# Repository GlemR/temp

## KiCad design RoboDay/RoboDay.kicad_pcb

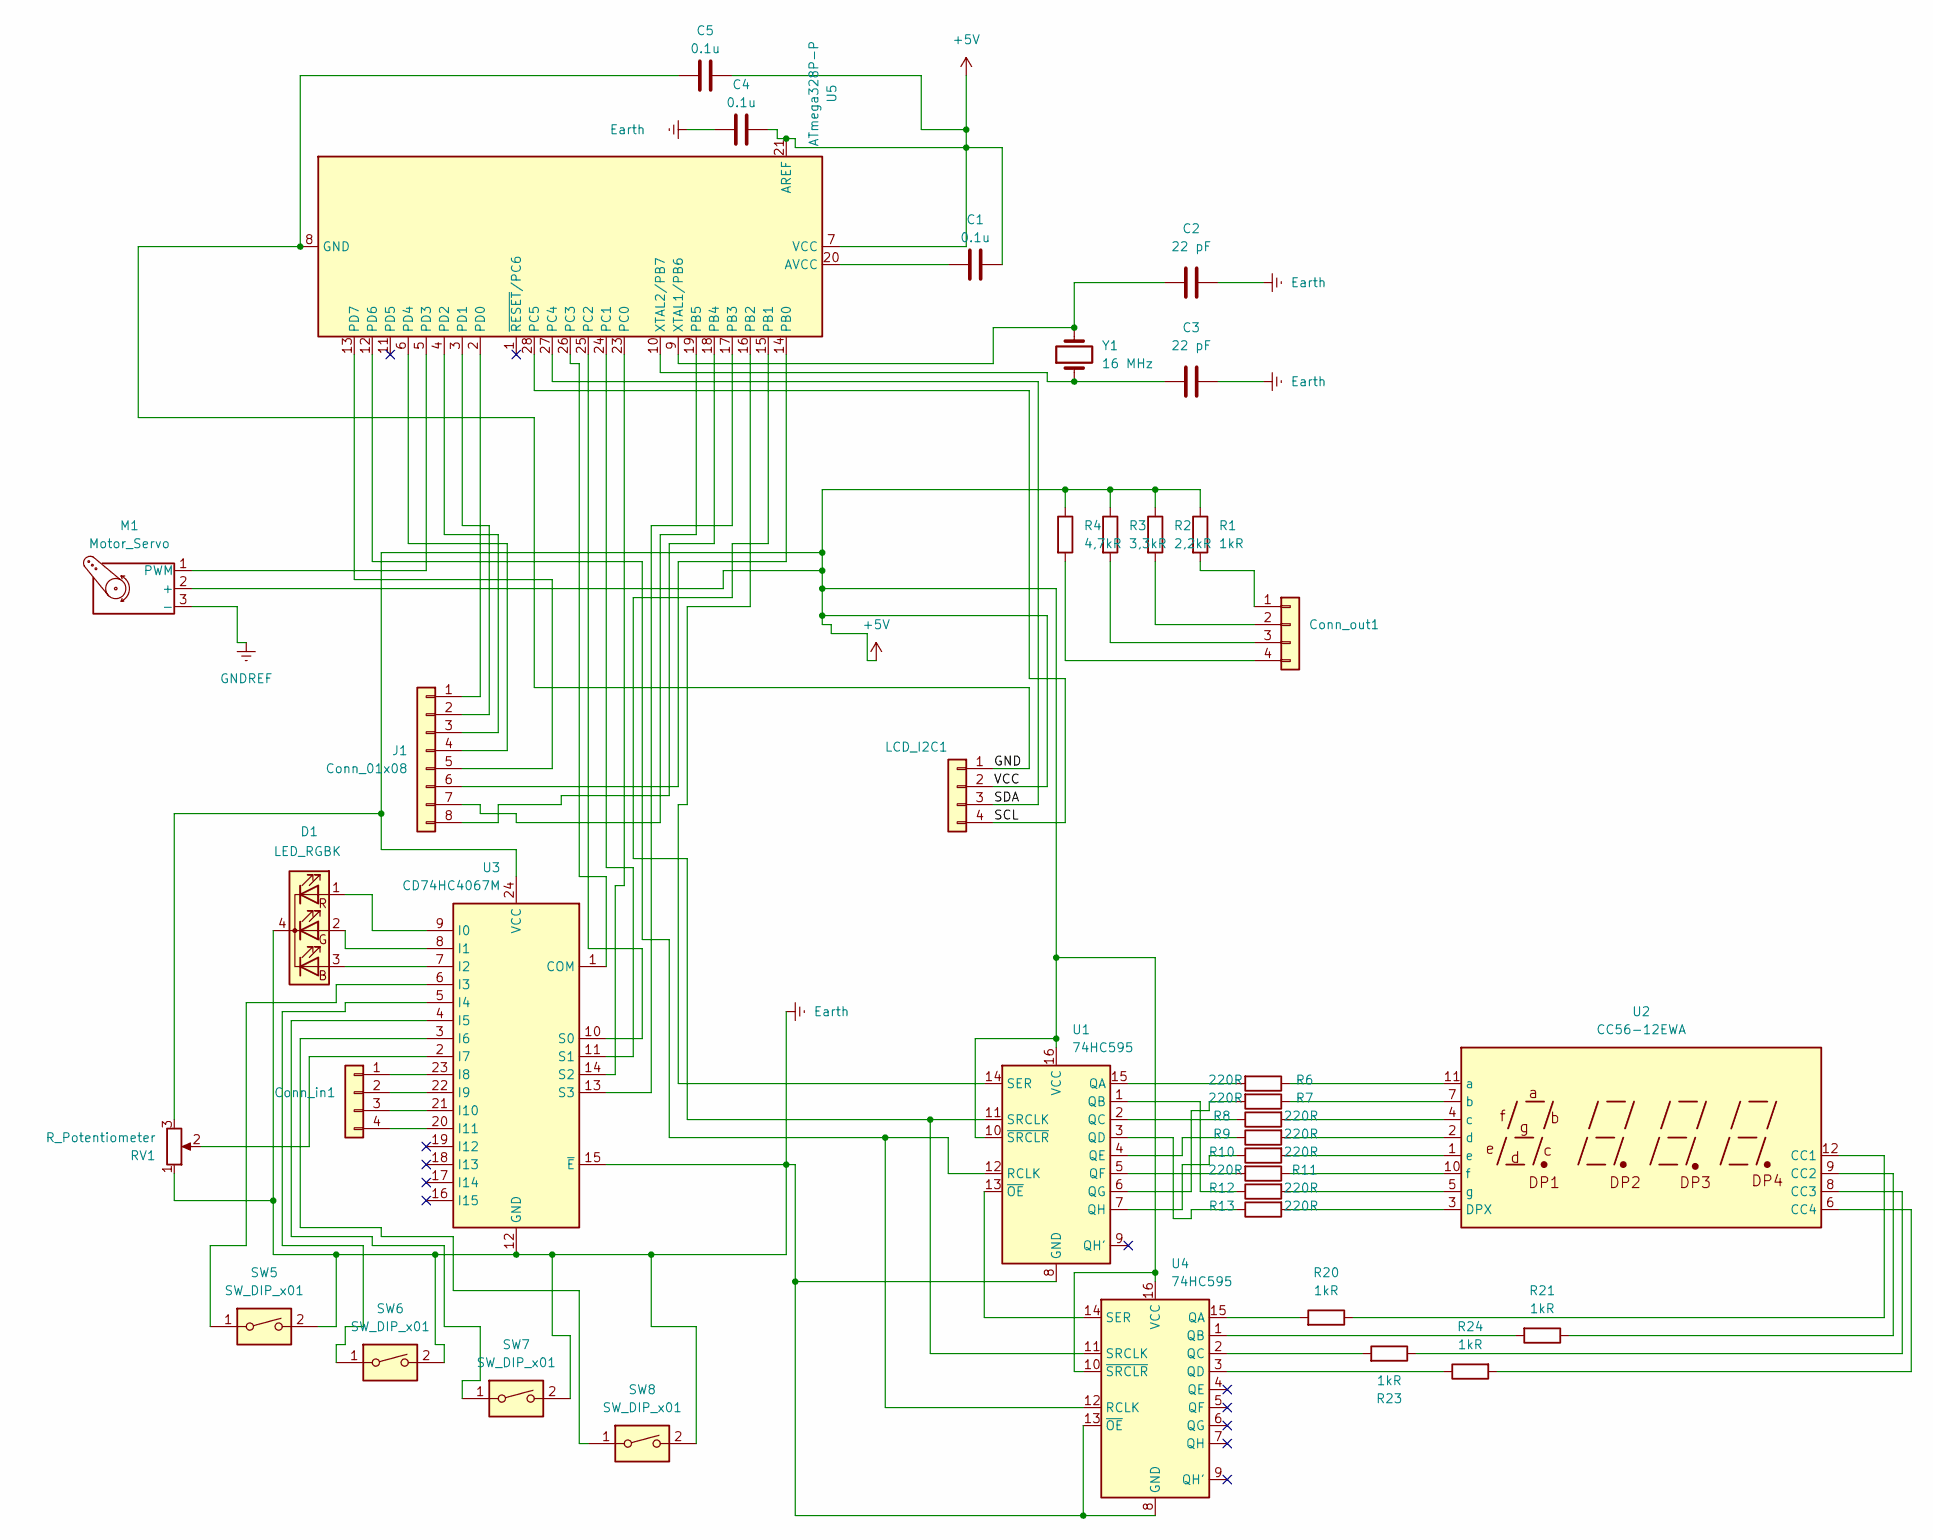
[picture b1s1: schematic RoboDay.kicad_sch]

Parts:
C1, C4, C5: 0.1u; CP_Radial_Tantal_D5.5mm_P2.50mm
C2, C3: 22 pF; CP_Radial_Tantal_D5.5mm_P2.50mm
Conn_in1: PinSocket_1x04_P2.54mm_Vertical
Conn_out1: PinSocket_1x04_P2.54mm_Vertical
D1: LED_RGBK; LED_BL-FL7680RGB
J1: Conn_01x08; PinSocket_1x08_P2.54mm_Vertical
LCD_I2C1: PinSocket_1x04_P2.54mm_Vertical
M1: Motor_Servo; PinSocket_1x03_P2.54mm_Vertical
R1, R20, R21, R23, R24: 1kR; R_Axial_DIN0207_L6.3mm_D2.5mm_P7.62mm_Horizontal
R2: 2,2kR; R_Axial_DIN0207_L6.3mm_D2.5mm_P7.62mm_Horizontal
R3: 3,3kR; R_Axial_DIN0207_L6.3mm_D2.5mm_P7.62mm_Horizontal
R4: 4,7kR; R_Axial_DIN0207_L6.3mm_D2.5mm_P7.62mm_Horizontal
R6, R7, R8, R9, R10, R11, R12, R13: 220R; R_Axial_DIN0207_L6.3mm_D2.5mm_P7.62mm_Horizontal
RV1: R_Potentiometer; Potentiometer_Piher_PC-16_Single_Horizontal
SW5, SW6, SW7, SW8: SW_DIP_x01; SW_PUSH-12mm
U1, U4: 74HC595; DIP-16_W10.16mm
U2: CC56-12EWA; CA56-12EWA
U3: CD74HC4067M; mux_16
U5: ATmega328P-P; DIP-28_W7.62mm
Y1: 16 MHz; Crystal_HC18-U_Vertical

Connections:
/GND: C5.2, LCD_I2C1.1, U5.8 (GND), U5.22 (GND)
/SCL: LCD_I2C1.4, U5.28 (PC5)
/SDA: LCD_I2C1.3, U5.27 (PC4)
Earth: C2.1, C3.1, C4.2, D1.4 (K), RV1.1, SW5.2, SW6.2, SW7.2, SW8.2, U1.8 (GND), U3.12 (GND), U3.15 (~E), U4.8 (GND), U4.13 (~OE)
GNDREF: M1.3 (-)
unnamed: Conn_in1.1, U3.23 (I8)
unnamed: Conn_in1.2, U3.22 (I9)
unnamed: Conn_in1.3, U3.21 (I10)
unnamed: Conn_in1.4, U3.20 (I11)
unnamed: Conn_out1.1, R1.2
unnamed: Conn_out1.2, R2.2
unnamed: Conn_out1.3, R3.2
unnamed: Conn_out1.4, R4.2
unnamed: D1.3 (BA), U3.7 (I2)
unnamed: D1.2 (GA), U3.8 (I1)
unnamed: D1.1 (RA), U3.9 (I0)
unnamed: J1.1, U5.2 (PD0)
unnamed: J1.2, U5.3 (PD1)
unnamed: J1.3, U5.4 (PD2)
unnamed: J1.4, U5.6 (PD4)
unnamed: J1.5, U5.13 (PD7)
unnamed: J1.6, U5.14 (PB0)
unnamed: J1.7, U5.19 (PB5)
unnamed: J1.8, U5.18 (PB4)
unnamed: M1.1 (PWM), U5.5 (PD3)
unnamed: R6.2, U1.15 (QA)
unnamed: R12.1, U1.1 (QB)
unnamed: R8.1, U1.2 (QC)
unnamed: R13.1, U1.3 (QD)
unnamed: R9.1, U1.4 (QE)
unnamed: R11.2, U1.5 (QF)
unnamed: R7.2, U1.6 (QG)
unnamed: R10.1, U1.7 (QH)
unnamed: U1.12 (RCLK), U4.12 (RCLK), U5.12 (PD6)
unnamed: U1.14 (SER), U5.16 (PB2)
unnamed: U1.11 (SRCLK), U4.11 (SRCLK), U5.15 (PB1)
unnamed: U1.13 (~OE), U4.14 (SER)
unnamed: R20.1, U2.12 (CC1)
unnamed: R21.1, U2.9 (CC2)
unnamed: R23.1, U2.8 (CC3)
unnamed: R24.2, U2.6 (CC4)
unnamed: R13.2, U2.3 (DPX)
unnamed: R6.1, U2.11 (a)
unnamed: R7.1, U2.7 (b)
unnamed: R8.2, U2.4 (c)
unnamed: R9.2, U2.2 (d)
unnamed: R10.2, U2.1 (e)
unnamed: R11.1, U2.10 (f)
unnamed: R12.2, U2.5 (g)
unnamed: U3.1 (COM), U5.26 (PC3)
unnamed: SW5.1, U3.6 (I3)
unnamed: SW6.1, U3.5 (I4)
unnamed: SW7.1, U3.4 (I5)
unnamed: SW8.1, U3.3 (I6)
unnamed: RV1.2, U3.2 (I7)
unnamed: U3.10 (S0), U5.25 (PC2)
unnamed: U3.11 (S1), U5.24 (PC1)
unnamed: U3.14 (S2), U5.23 (PC0)
unnamed: U3.13 (S3), U5.17 (PB3)
unnamed: R20.2, U4.15 (QA)
unnamed: R21.2, U4.1 (QB)
unnamed: R23.2, U4.2 (QC)
unnamed: R24.1, U4.3 (QD)
unnamed: C1.2, U5.20 (AVCC)
unnamed: C2.2, U5.9 (XTAL1/PB6), Y1.2
unnamed: C3.2, U5.10 (XTAL2/PB7), Y1.1

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
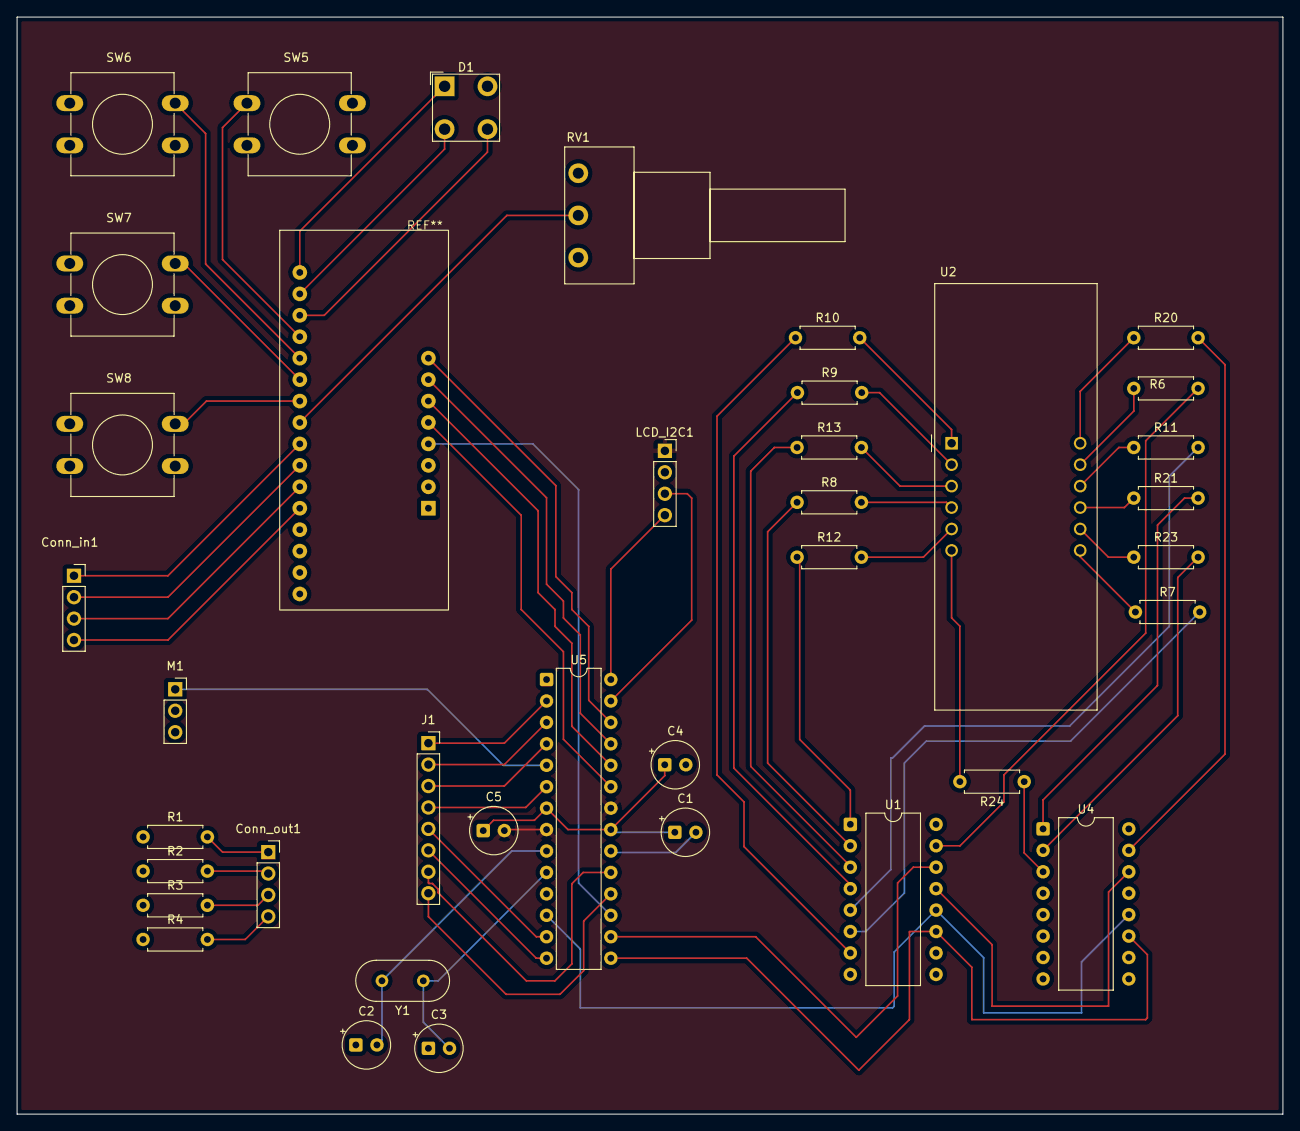
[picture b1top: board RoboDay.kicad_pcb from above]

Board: 2 copper layers, 150.0 x 130.0 mm, 38 parts (0 on the bottom side), 67 nets.

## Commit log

2025-05-06 memory
2025-05-06 forgor
2025-05-10 cables and memory
2025-05-12 quick fix
2025-05-17 kicad
2025-06-03 finale demo
